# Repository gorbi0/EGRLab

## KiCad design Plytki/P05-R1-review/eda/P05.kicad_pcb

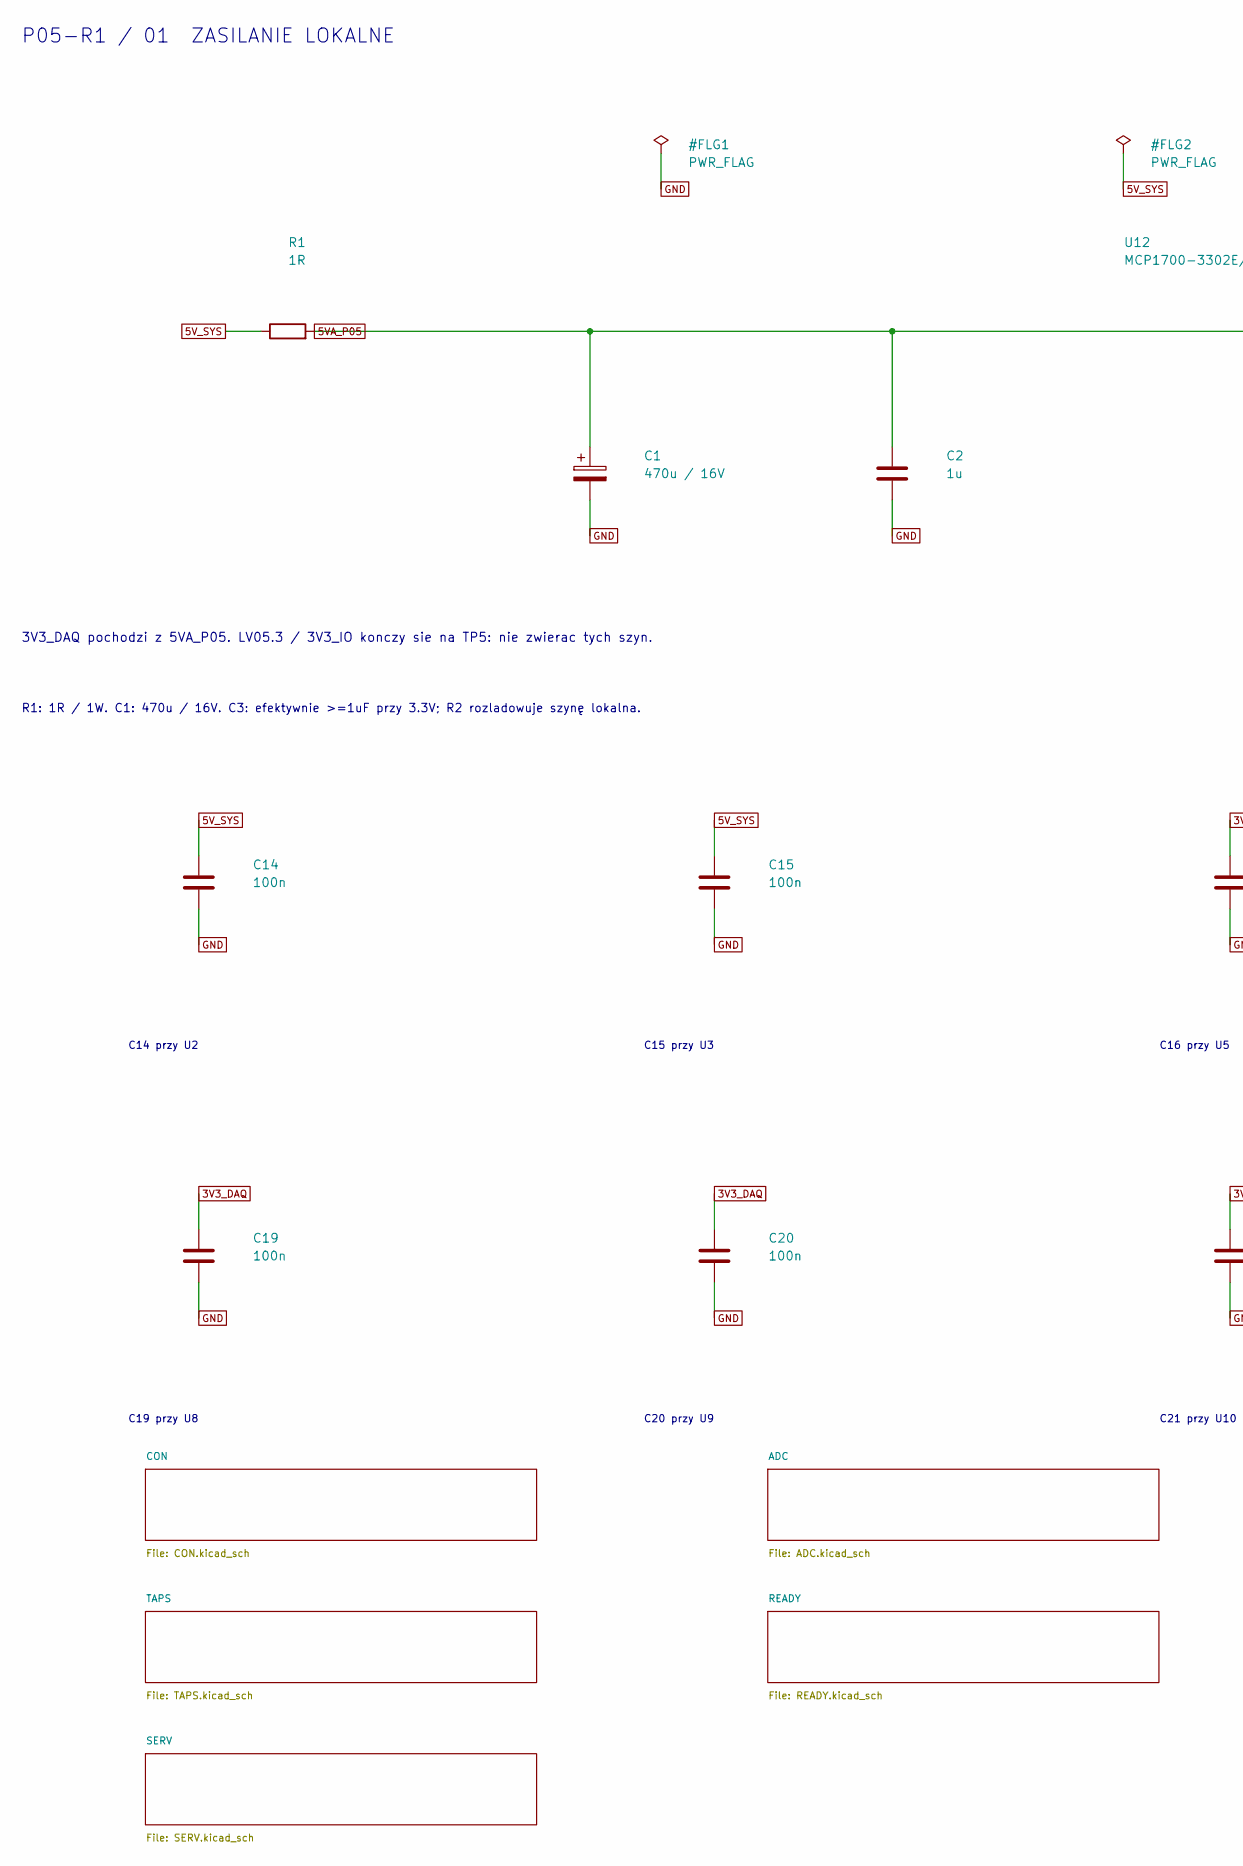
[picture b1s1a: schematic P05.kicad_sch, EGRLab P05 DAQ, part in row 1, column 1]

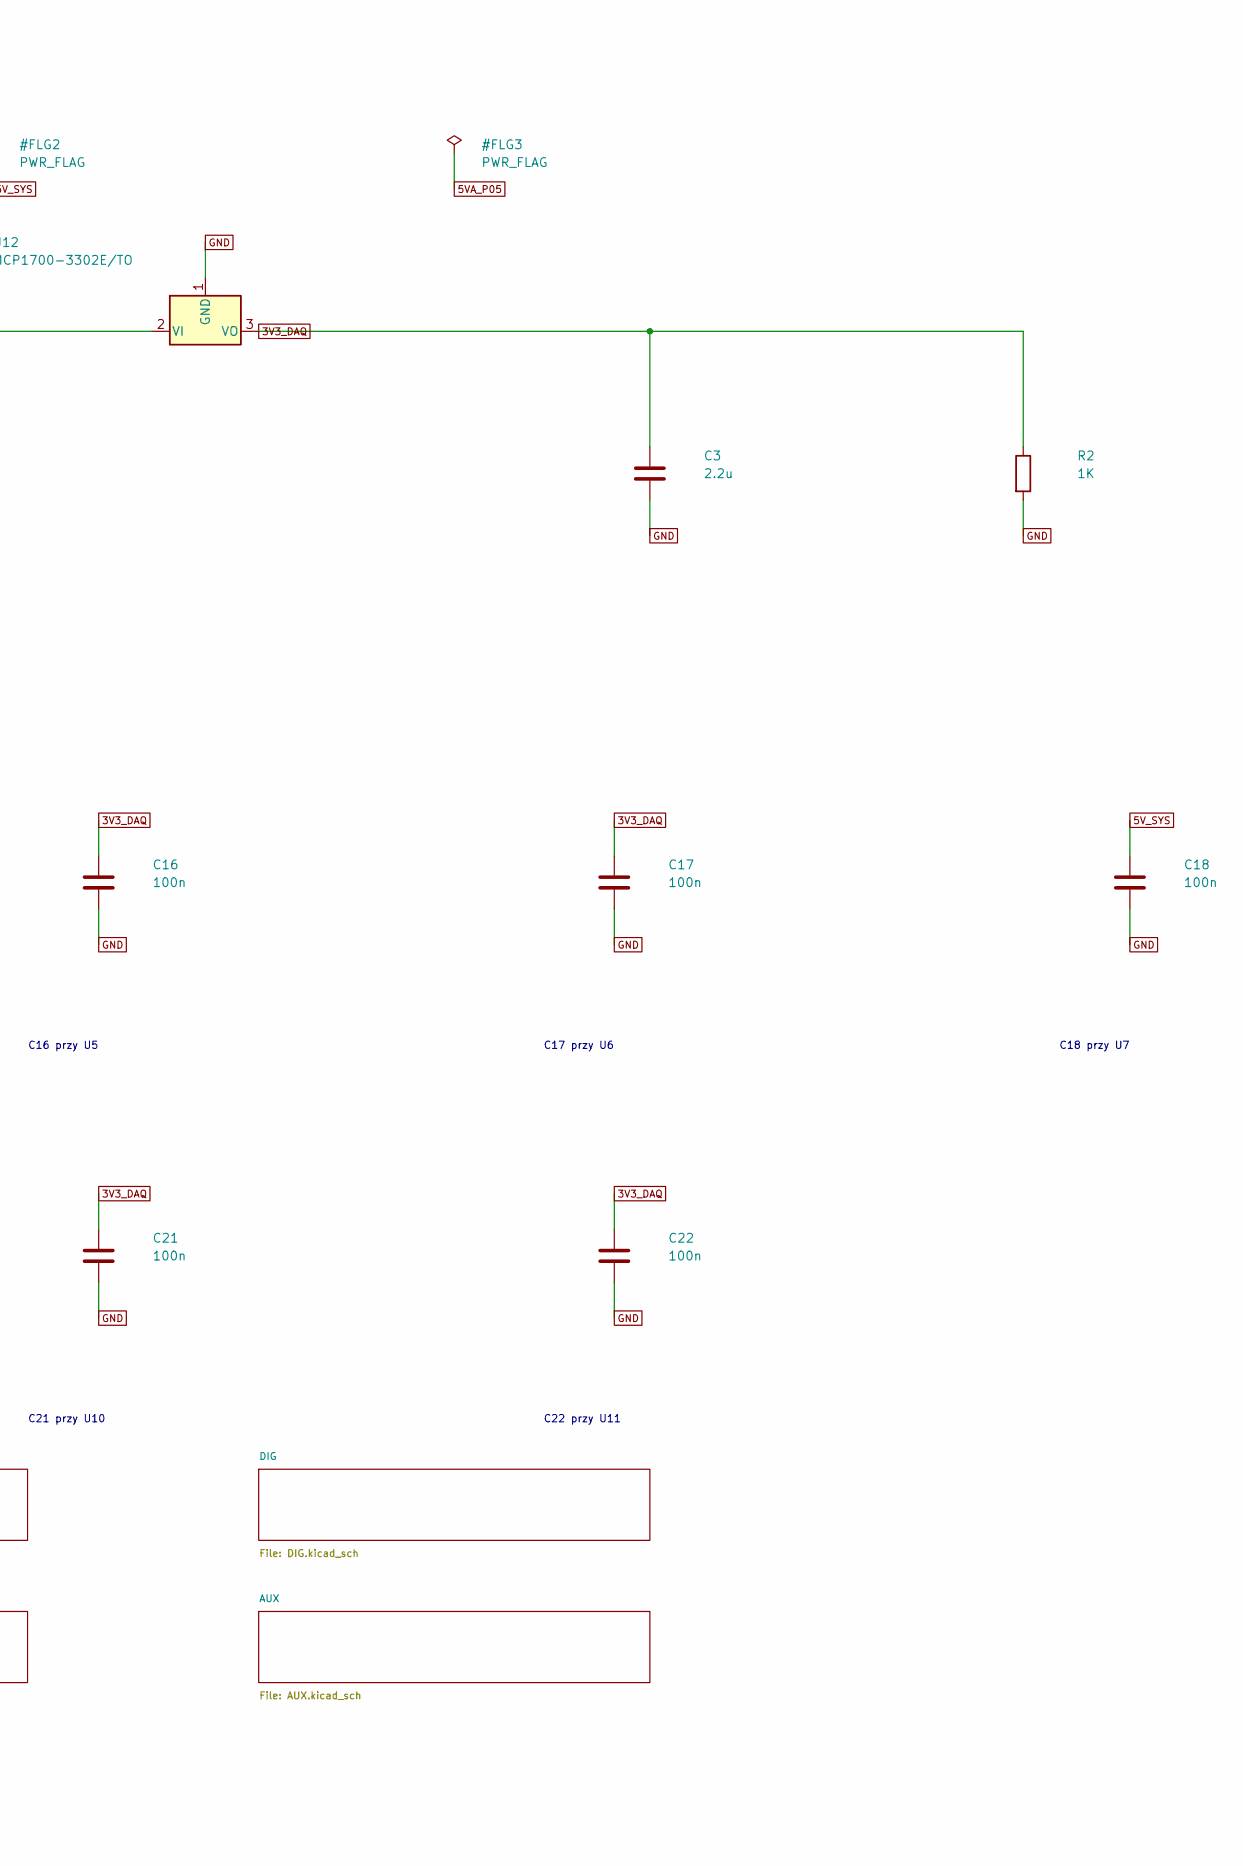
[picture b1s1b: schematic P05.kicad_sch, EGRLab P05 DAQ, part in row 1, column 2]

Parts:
C1: 470u / 16V; CP_Radial_D8.0mm_P3.50mm; MPN EEUFR1C471
C2: 1u; C_0805_2012Metric; MPN X7R 25V 10% 1u
C3: 2.2u; C_0805_2012Metric; MPN X7R 25V 10% 2.2u
C14, C15, C16, C17, C18, C19, C20, C21, C22: 100n; C_0805_2012Metric; MPN X7R 25V 10% 100n
R1: 1R; R_Axial_DIN0411_L9.9mm_D3.6mm_P15.24mm_Horizontal; MPN metal film resistor 1R 1%
R2: 1K; R_Axial_DIN0207_L6.3mm_D2.5mm_P10.16mm_Horizontal; MPN metal film resistor 1K 1%
U12: MCP1700-3302E/TO; TO-92_Inline_Wide; MPN MCP1700-3302E/TO

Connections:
3V3_DAQ: C3.1, C16.1, C17.1, C19.1, C20.1, C21.1, C22.1, R2.1, U12.3 (VO); also elsewhere on the board
5VA_P05: C1.1, C2.1, R1.2, U12.2 (VI); also elsewhere on the board
5V_SYS: C14.1, C15.1, C18.1, R1.1; also elsewhere on the board
GND: C1.2, C2.2, C3.2, C14.2, C15.2, C16.2, C17.2, C18.2, C19.2, C20.2, C21.2, C22.2, R2.2, U12.1 (GND); also elsewhere on the board

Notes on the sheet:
C14 przy U2
C15 przy U3
C16 przy U5
C17 przy U6
C18 przy U7
C19 przy U8
C20 przy U9
C21 przy U10
C22 przy U11
3V3_DAQ pochodzi z 5VA_P05. LV05.3 / 3V3_IO konczy sie na TP5: nie zwierac tych szyn.
R1: 1R / 1W. C1: 470u / 16V. C3: efektywnie >=1uF przy 3.3V; R2 rozladowuje szynę lokalna.
P05-R1 / 01 ZASILANIE LOKALNE

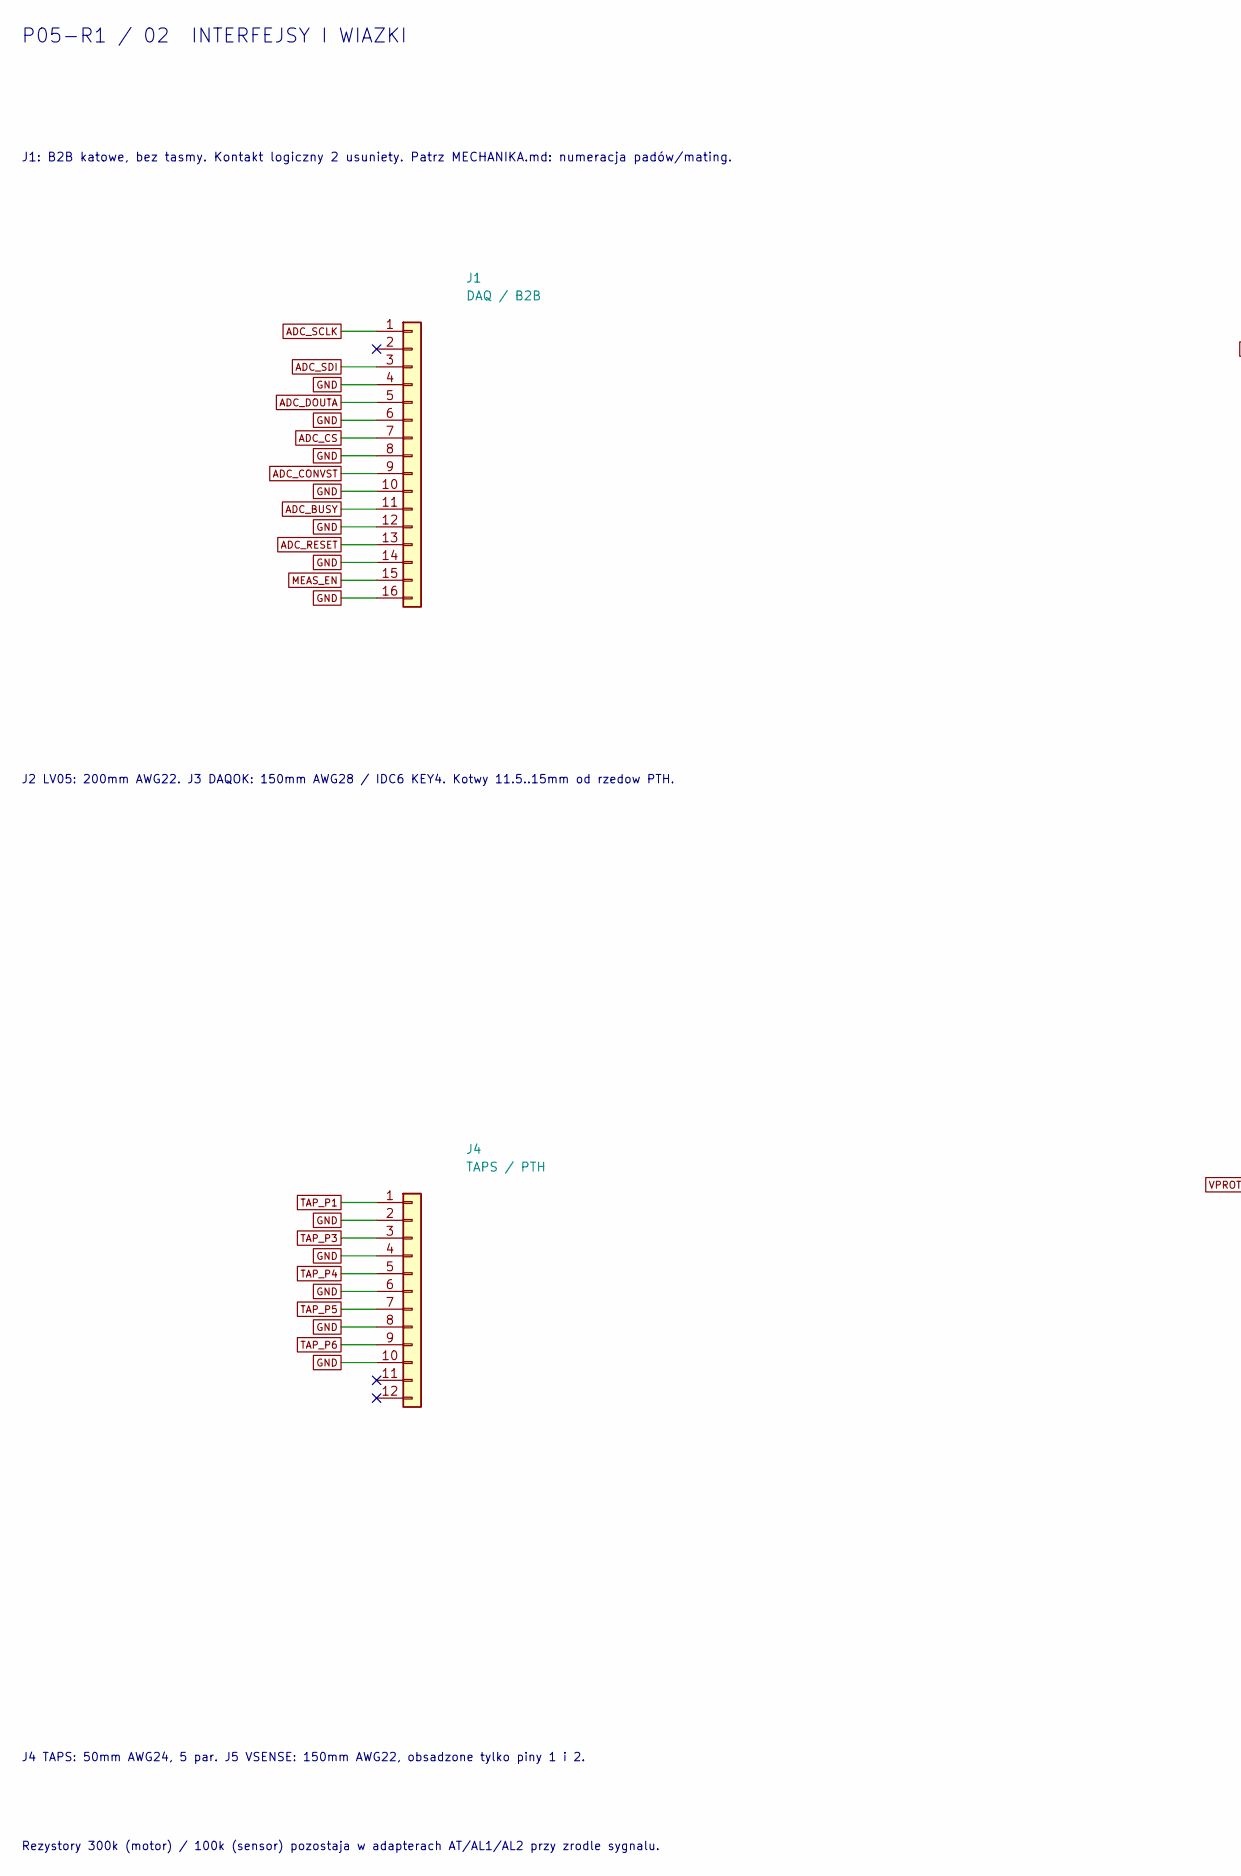
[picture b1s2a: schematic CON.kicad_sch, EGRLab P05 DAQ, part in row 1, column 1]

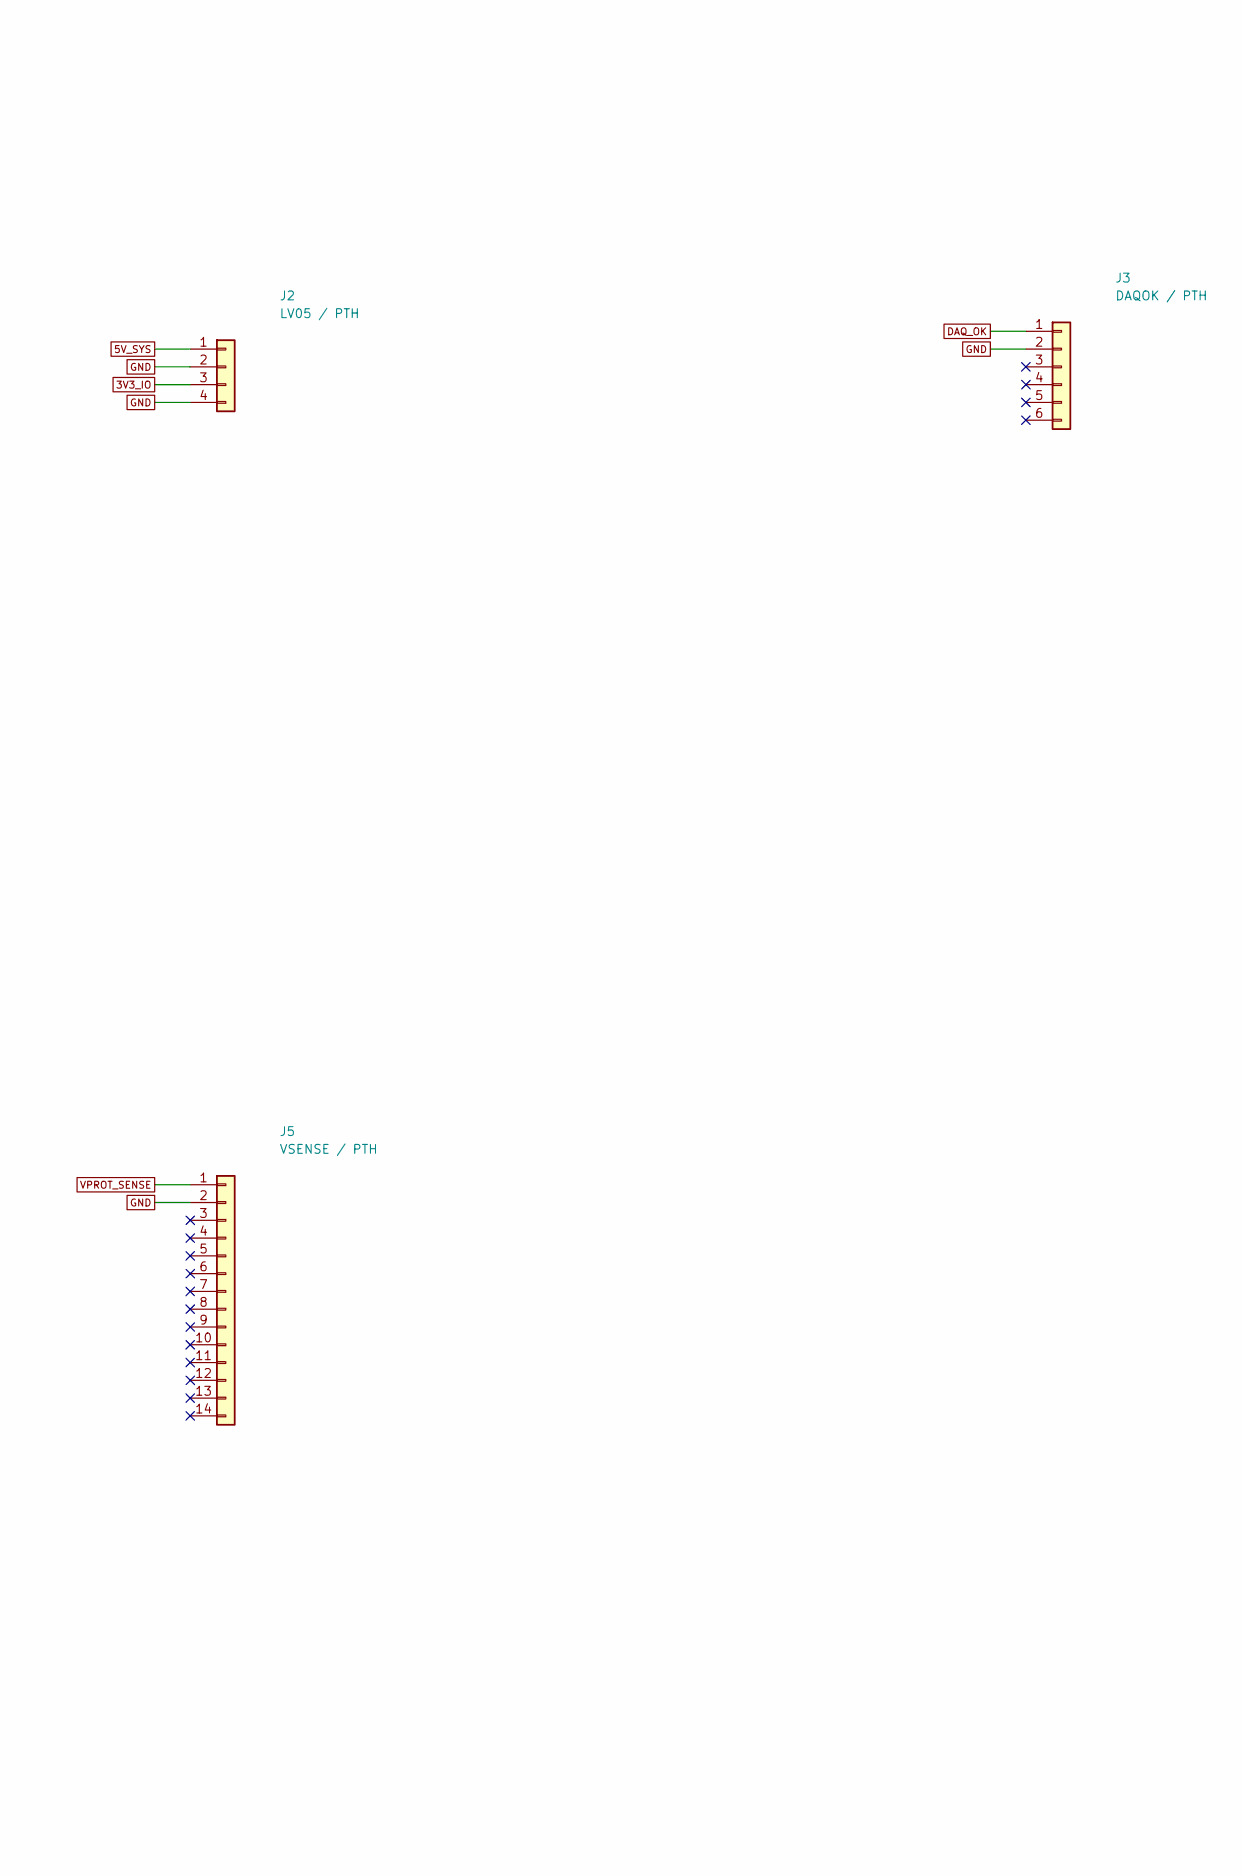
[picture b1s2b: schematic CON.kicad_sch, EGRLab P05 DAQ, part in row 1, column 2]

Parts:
J1: DAQ / B2B; DAQ_TSW_NA_2x8; MPN TSW-108-08-G-D-NA
J2: LV05 / PTH; PTH_LV05_4; MPN harness AWG22
J3: DAQOK / PTH; PTH_DAQOK_6; MPN ribbon AWG28
J4: TAPS / PTH; PTH_TAPS_12; MPN 5 pairs AWG24
J5: VSENSE / PTH; PTH_VSENSE_14; MPN AWG22 pair, only positions 1/2 populated

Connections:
3V3_IO: J2.3; also elsewhere on the board
5V_SYS: J2.1; also elsewhere on the board
ADC_BUSY: J1.11; also elsewhere on the board
ADC_CONVST: J1.9; also elsewhere on the board
ADC_CS: J1.7; also elsewhere on the board
ADC_DOUTA: J1.5; also elsewhere on the board
ADC_RESET: J1.13; also elsewhere on the board
ADC_SCLK: J1.1; also elsewhere on the board
ADC_SDI: J1.3; also elsewhere on the board
DAQ_OK: J3.1; also elsewhere on the board
GND: J1.4, J1.6, J1.8, J1.10, J1.12, J1.14, J1.16, J2.2, J2.4, J3.2, J4.2, J4.4, J4.6, J4.8, J4.10, J5.2; also elsewhere on the board
MEAS_EN: J1.15; also elsewhere on the board
TAP_P1: J4.1; also elsewhere on the board
TAP_P3: J4.3; also elsewhere on the board
TAP_P4: J4.5; also elsewhere on the board
TAP_P5: J4.7; also elsewhere on the board
TAP_P6: J4.9; also elsewhere on the board
VPROT_SENSE: J5.1; also elsewhere on the board

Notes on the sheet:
J1: B2B katowe, bez tasmy. Kontakt logiczny 2 usuniety. Patrz MECHANIKA.md: numeracja padów/mating.
J2 LV05: 200mm AWG22. J3 DAQOK: 150mm AWG28 / IDC6 KEY4. Kotwy 11.5..15mm od rzedow PTH.
J4 TAPS: 50mm AWG24, 5 par. J5 VSENSE: 150mm AWG22, obsadzone tylko piny 1 i 2.
Rezystory 300k (motor) / 100k (sensor) pozostaja w adapterach AT/AL1/AL2 przy zrodle sygnalu.
P05-R1 / 02 INTERFEJSY I WIAZKI

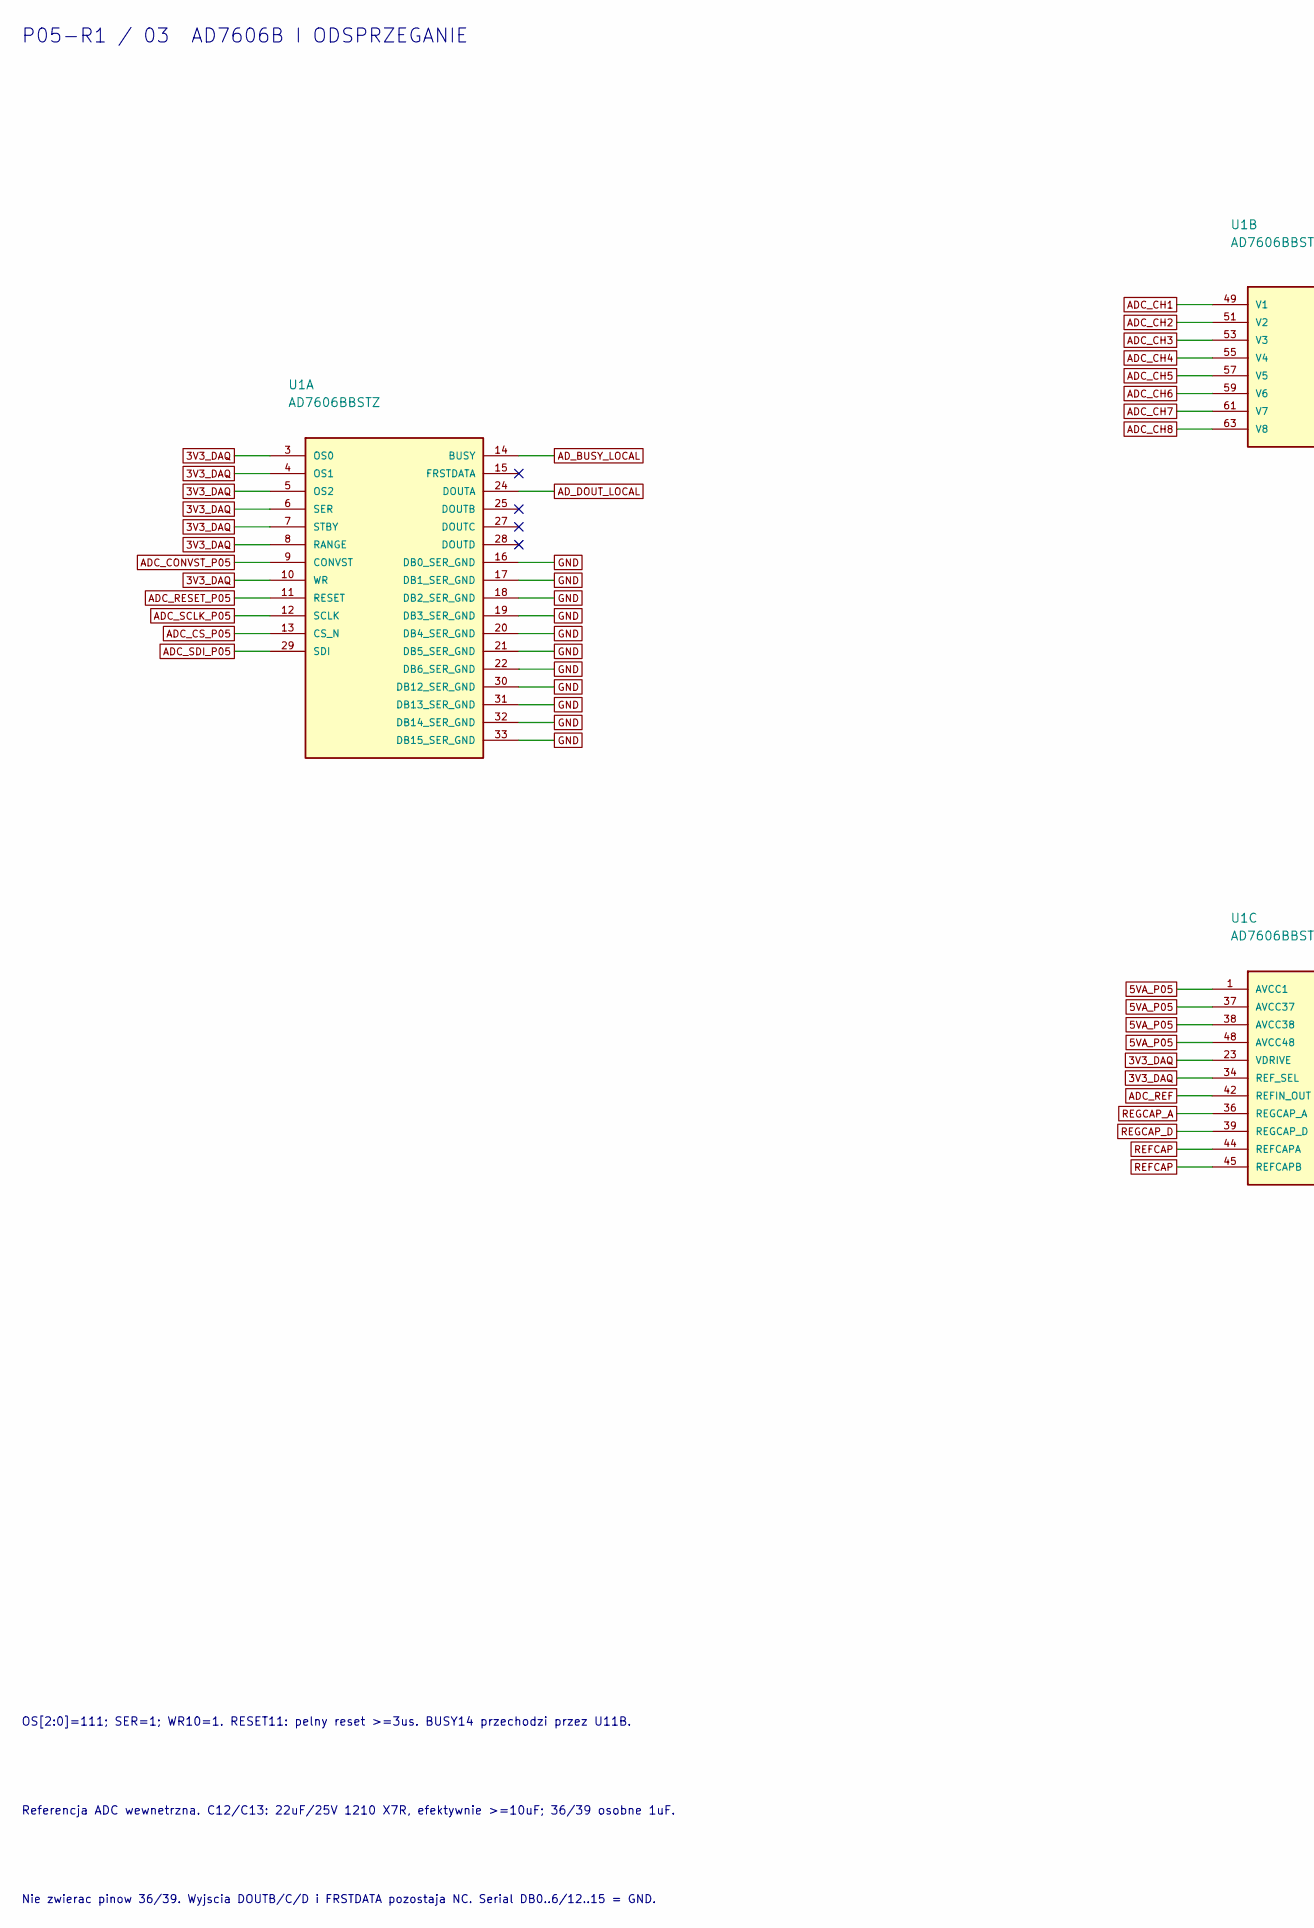
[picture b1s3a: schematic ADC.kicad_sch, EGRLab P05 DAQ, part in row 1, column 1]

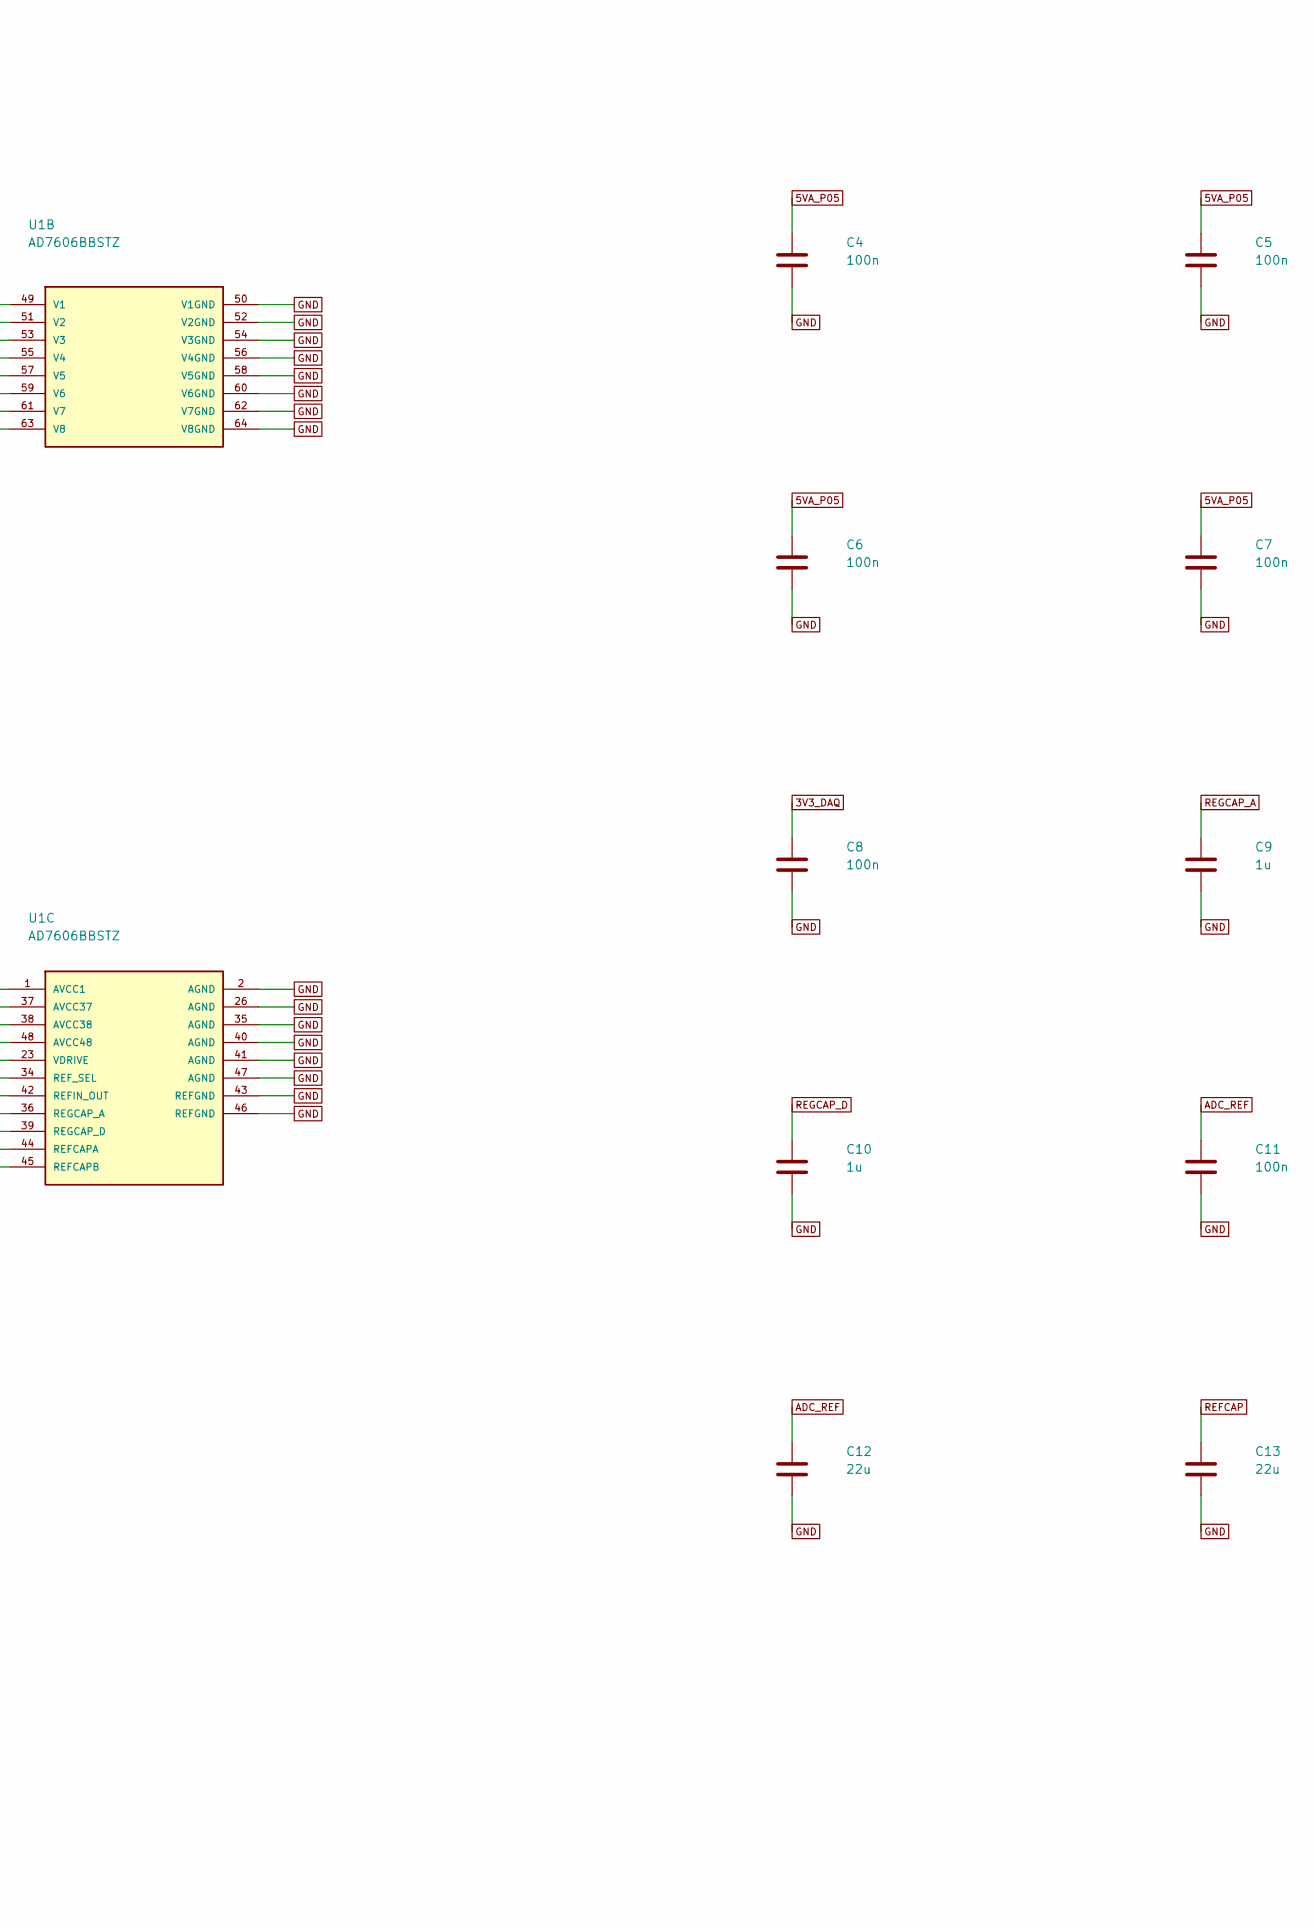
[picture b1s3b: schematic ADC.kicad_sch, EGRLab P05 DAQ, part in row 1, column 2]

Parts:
C4, C5, C6, C7, C8, C11: 100n; C_0603_1608Metric; MPN X7R 25V 10% 100n
C9, C10: 1u; C_0805_2012Metric; MPN X7R 25V 10% 1u
C12, C13: 22u; C_1210_3225Metric; MPN C3225X7R1E226M250AB
U1: AD7606BBSTZ; LQFP-64_10x10mm_P0.5mm; MPN AD7606BBSTZ

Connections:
3V3_DAQ: C8.1, U1.3 (OS0), U1.4 (OS1), U1.5 (OS2), U1.6 (SER), U1.7 (STBY), U1.8 (RANGE), U1.10 (WR), U1.23 (VDRIVE), U1.34 (REF_SEL); also elsewhere on the board
5VA_P05: C4.1, C5.1, C6.1, C7.1, U1.1 (AVCC1), U1.37 (AVCC37), U1.38 (AVCC38), U1.48 (AVCC48); also elsewhere on the board
ADC_CH1: U1.49 (V1); also elsewhere on the board
ADC_CH2: U1.51 (V2); also elsewhere on the board
ADC_CH3: U1.53 (V3); also elsewhere on the board
ADC_CH4: U1.55 (V4); also elsewhere on the board
ADC_CH5: U1.57 (V5); also elsewhere on the board
ADC_CH6: U1.59 (V6); also elsewhere on the board
ADC_CH7: U1.61 (V7); also elsewhere on the board
ADC_CH8: U1.63 (V8); also elsewhere on the board
ADC_CONVST_P05: U1.9 (CONVST); also elsewhere on the board
ADC_CS_P05: U1.13 (CS_N); also elsewhere on the board
ADC_REF: C11.1, C12.1, U1.42 (REFIN_OUT); also elsewhere on the board
ADC_RESET_P05: U1.11 (RESET); also elsewhere on the board
ADC_SCLK_P05: U1.12 (SCLK); also elsewhere on the board
ADC_SDI_P05: U1.29 (SDI); also elsewhere on the board
AD_BUSY_LOCAL: U1.14 (BUSY); also elsewhere on the board
AD_DOUT_LOCAL: U1.24 (DOUTA); also elsewhere on the board
GND: C4.2, C5.2, C6.2, C7.2, C8.2, C9.2, C10.2, C11.2, C12.2, C13.2, U1.2 (AGND), U1.16 (DB0_SER_GND), U1.17 (DB1_SER_GND), U1.18 (DB2_SER_GND), U1.19 (DB3_SER_GND), U1.20 (DB4_SER_GND), U1.21 (DB5_SER_GND), U1.22 (DB6_SER_GND), U1.26 (AGND), U1.30 (DB12_SER_GND), U1.31 (DB13_SER_GND), U1.32 (DB14_SER_GND), U1.33 (DB15_SER_GND), U1.35 (AGND), U1.40 (AGND), U1.41 (AGND), U1.43 (REFGND), U1.46 (REFGND), U1.47 (AGND), U1.50 (V1GND), U1.52 (V2GND), U1.54 (V3GND), U1.56 (V4GND), U1.58 (V5GND), U1.60 (V6GND), U1.62 (V7GND), U1.64 (V8GND); also elsewhere on the board
REFCAP: C13.1, U1.44 (REFCAPA), U1.45 (REFCAPB); also elsewhere on the board
REGCAP_A: C9.1, U1.36 (REGCAP_A); also elsewhere on the board
REGCAP_D: C10.1, U1.39 (REGCAP_D); also elsewhere on the board

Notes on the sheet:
OS[2:0]=111; SER=1; WR10=1. RESET11: pelny reset >=3us. BUSY14 przechodzi przez U11B.
Referencja ADC wewnetrzna. C12/C13: 22uF/25V 1210 X7R, efektywnie >=10uF; 36/39 osobne 1uF.
Nie zwierac pinow 36/39. Wyjscia DOUTB/C/D i FRSTDATA pozostaja NC. Serial DB0..6/12..15 = GND.
P05-R1 / 03 AD7606B I ODSPRZEGANIE

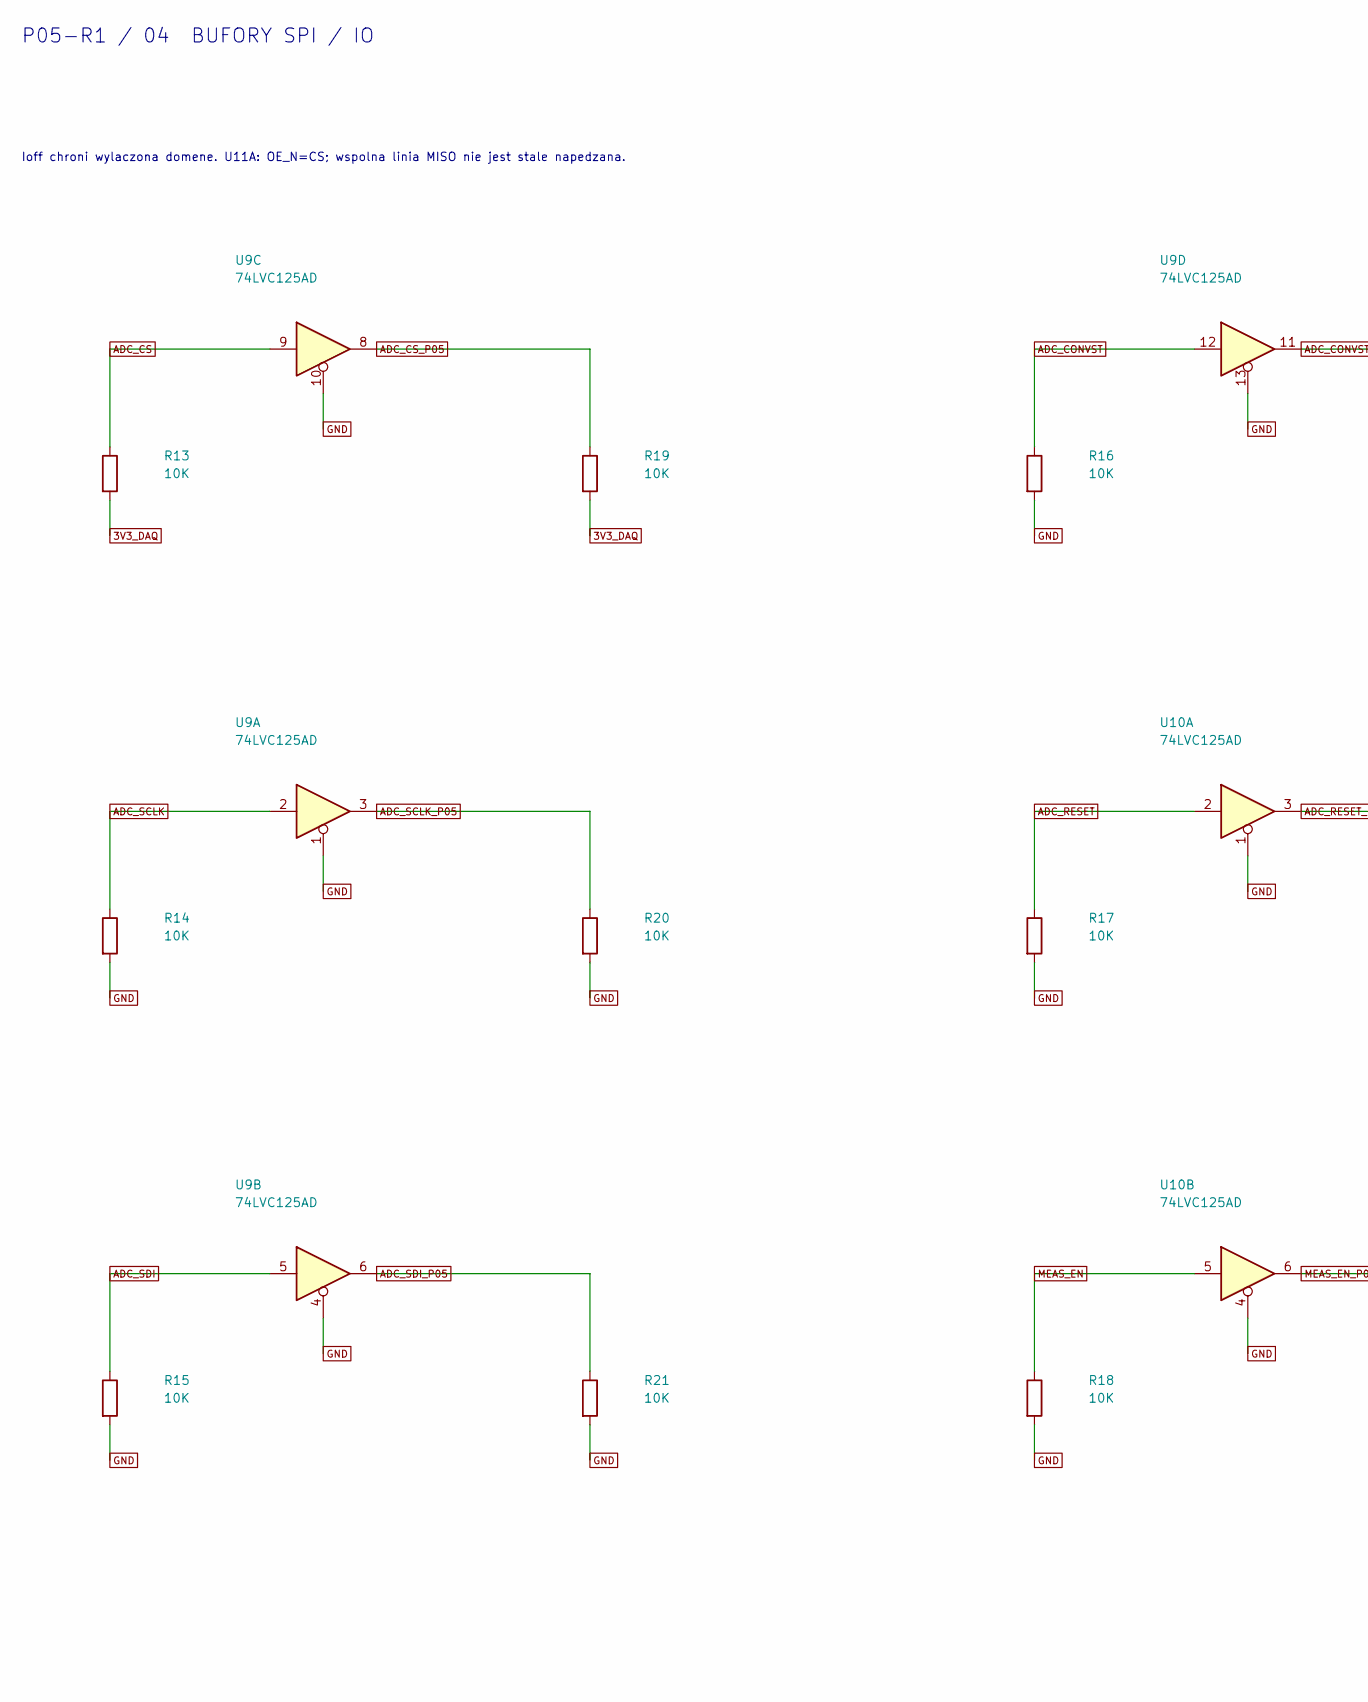
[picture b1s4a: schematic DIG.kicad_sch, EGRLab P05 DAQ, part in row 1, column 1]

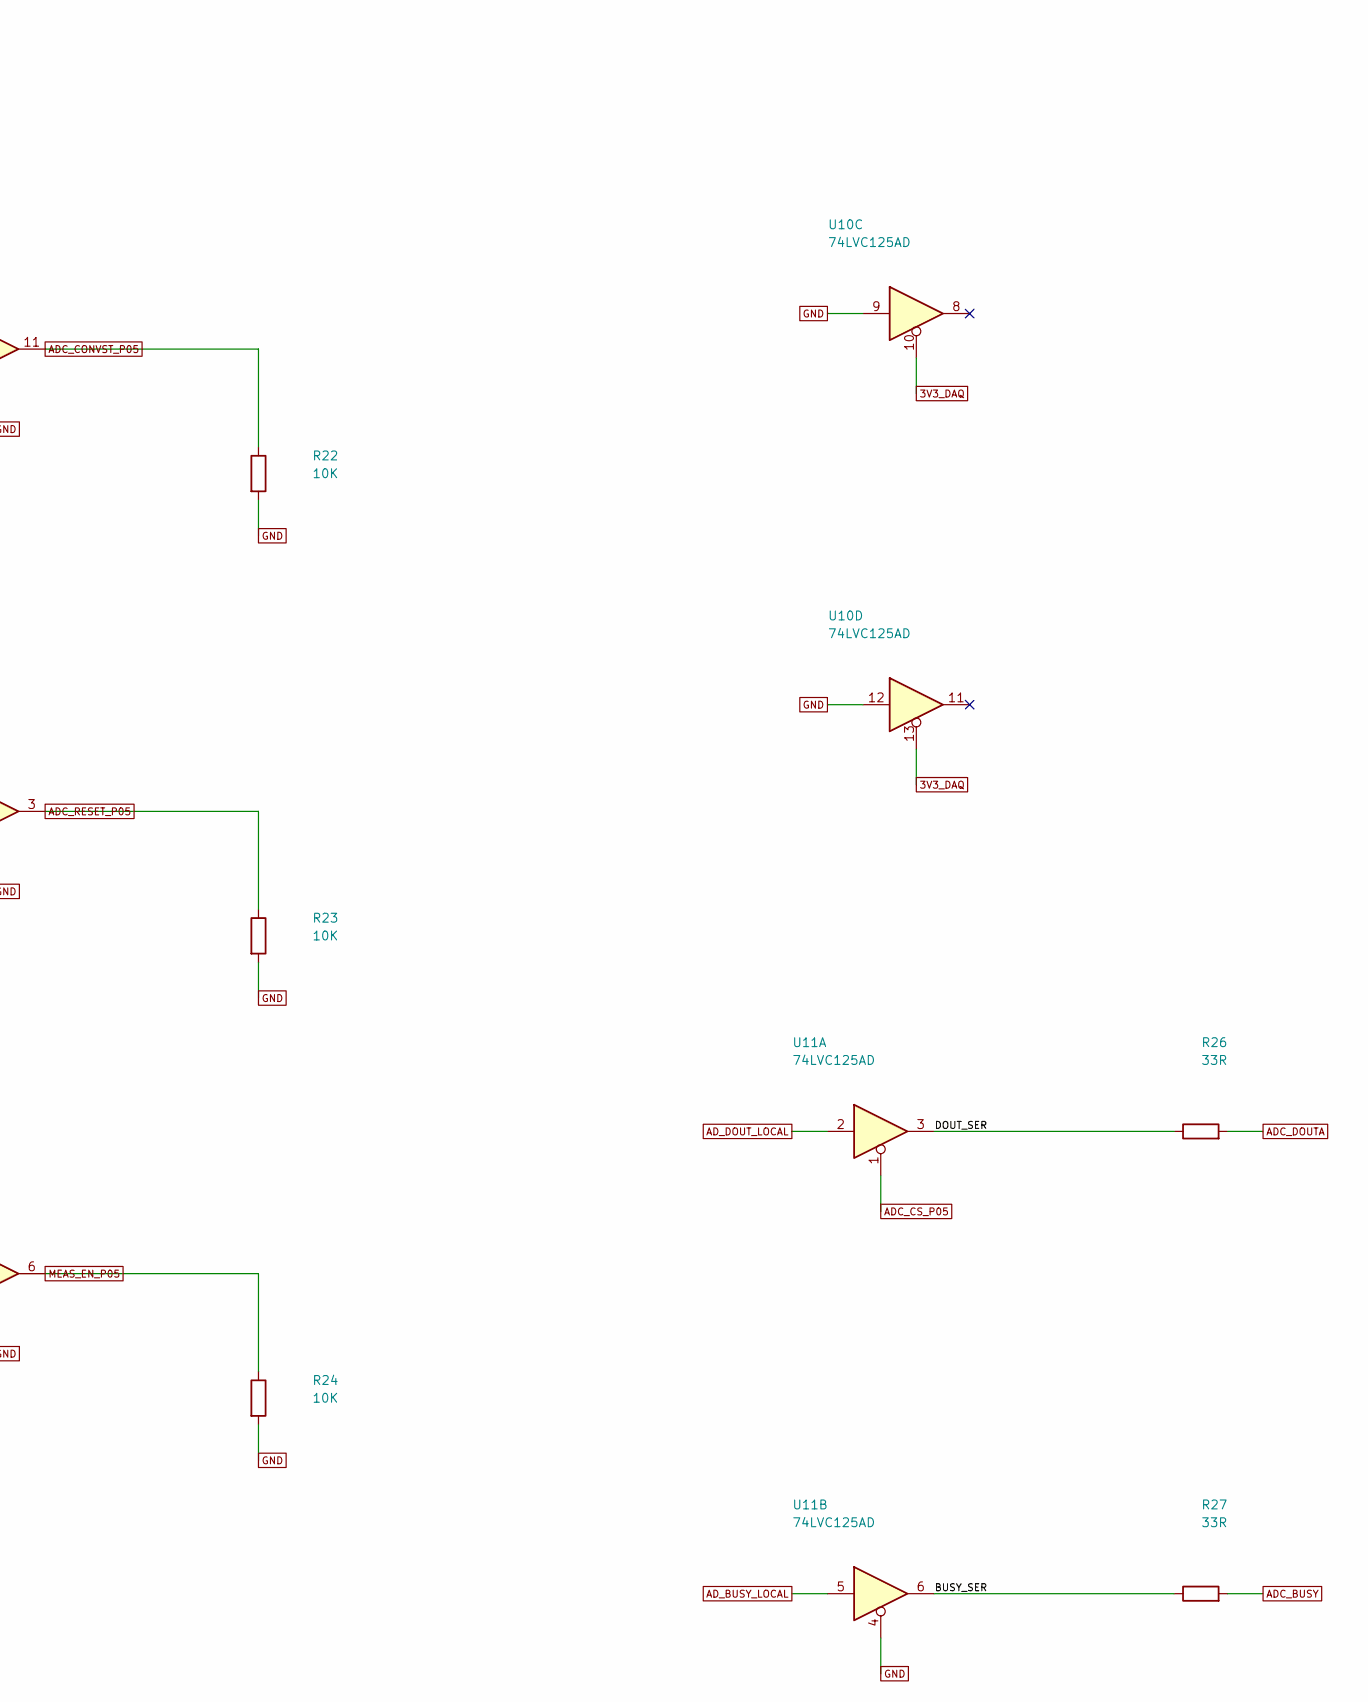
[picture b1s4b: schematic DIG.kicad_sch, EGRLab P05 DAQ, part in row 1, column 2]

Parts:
R13, R14, R15, R16, R17, R18, R19, R20, R21, R22, R23, R24: 10K; R_Axial_DIN0207_L6.3mm_D2.5mm_P10.16mm_Horizontal; MPN metal film resistor 10K 1%
R26, R27: 33R; R_0805_2012Metric; MPN 0805 1% 0.125W 33R
U9, U10, U11: 74LVC125AD; SOIC-14_3.9x8.7mm_P1.27mm; MPN 74LVC125AD,118

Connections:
3V3_DAQ: R13.2, R19.2, U10.10, U10.13; also elsewhere on the board
/DIG/BUSY_SER: R27.1, U11.6
/DIG/DOUT_SER: R26.1, U11.3
ADC_BUSY: R27.2; also elsewhere on the board
ADC_CONVST: R16.1, U9.12; also elsewhere on the board
ADC_CONVST_P05: R22.1, U9.11; also elsewhere on the board
ADC_CS: R13.1, U9.9; also elsewhere on the board
ADC_CS_P05: R19.1, U9.8, U11.1; also elsewhere on the board
ADC_DOUTA: R26.2; also elsewhere on the board
ADC_RESET: R17.1, U10.2; also elsewhere on the board
ADC_RESET_P05: R23.1, U10.3; also elsewhere on the board
ADC_SCLK: R14.1, U9.2; also elsewhere on the board
ADC_SCLK_P05: R20.1, U9.3; also elsewhere on the board
ADC_SDI: R15.1, U9.5; also elsewhere on the board
ADC_SDI_P05: R21.1, U9.6; also elsewhere on the board
AD_BUSY_LOCAL: U11.5; also elsewhere on the board
AD_DOUT_LOCAL: U11.2; also elsewhere on the board
GND: R14.2, R15.2, R16.2, R17.2, R18.2, R20.2, R21.2, R22.2, R23.2, R24.2, U9.1, U9.4, U9.10, U9.13, U10.1, U10.4, U10.9, U10.12, U11.4; also elsewhere on the board
MEAS_EN: R18.1, U10.5; also elsewhere on the board
MEAS_EN_P05: R24.1, U10.6; also elsewhere on the board

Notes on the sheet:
Ioff chroni wylaczona domene. U11A: OE_N=CS; wspolna linia MISO nie jest stale napedzana.
P05-R1 / 04 BUFORY SPI / IO
